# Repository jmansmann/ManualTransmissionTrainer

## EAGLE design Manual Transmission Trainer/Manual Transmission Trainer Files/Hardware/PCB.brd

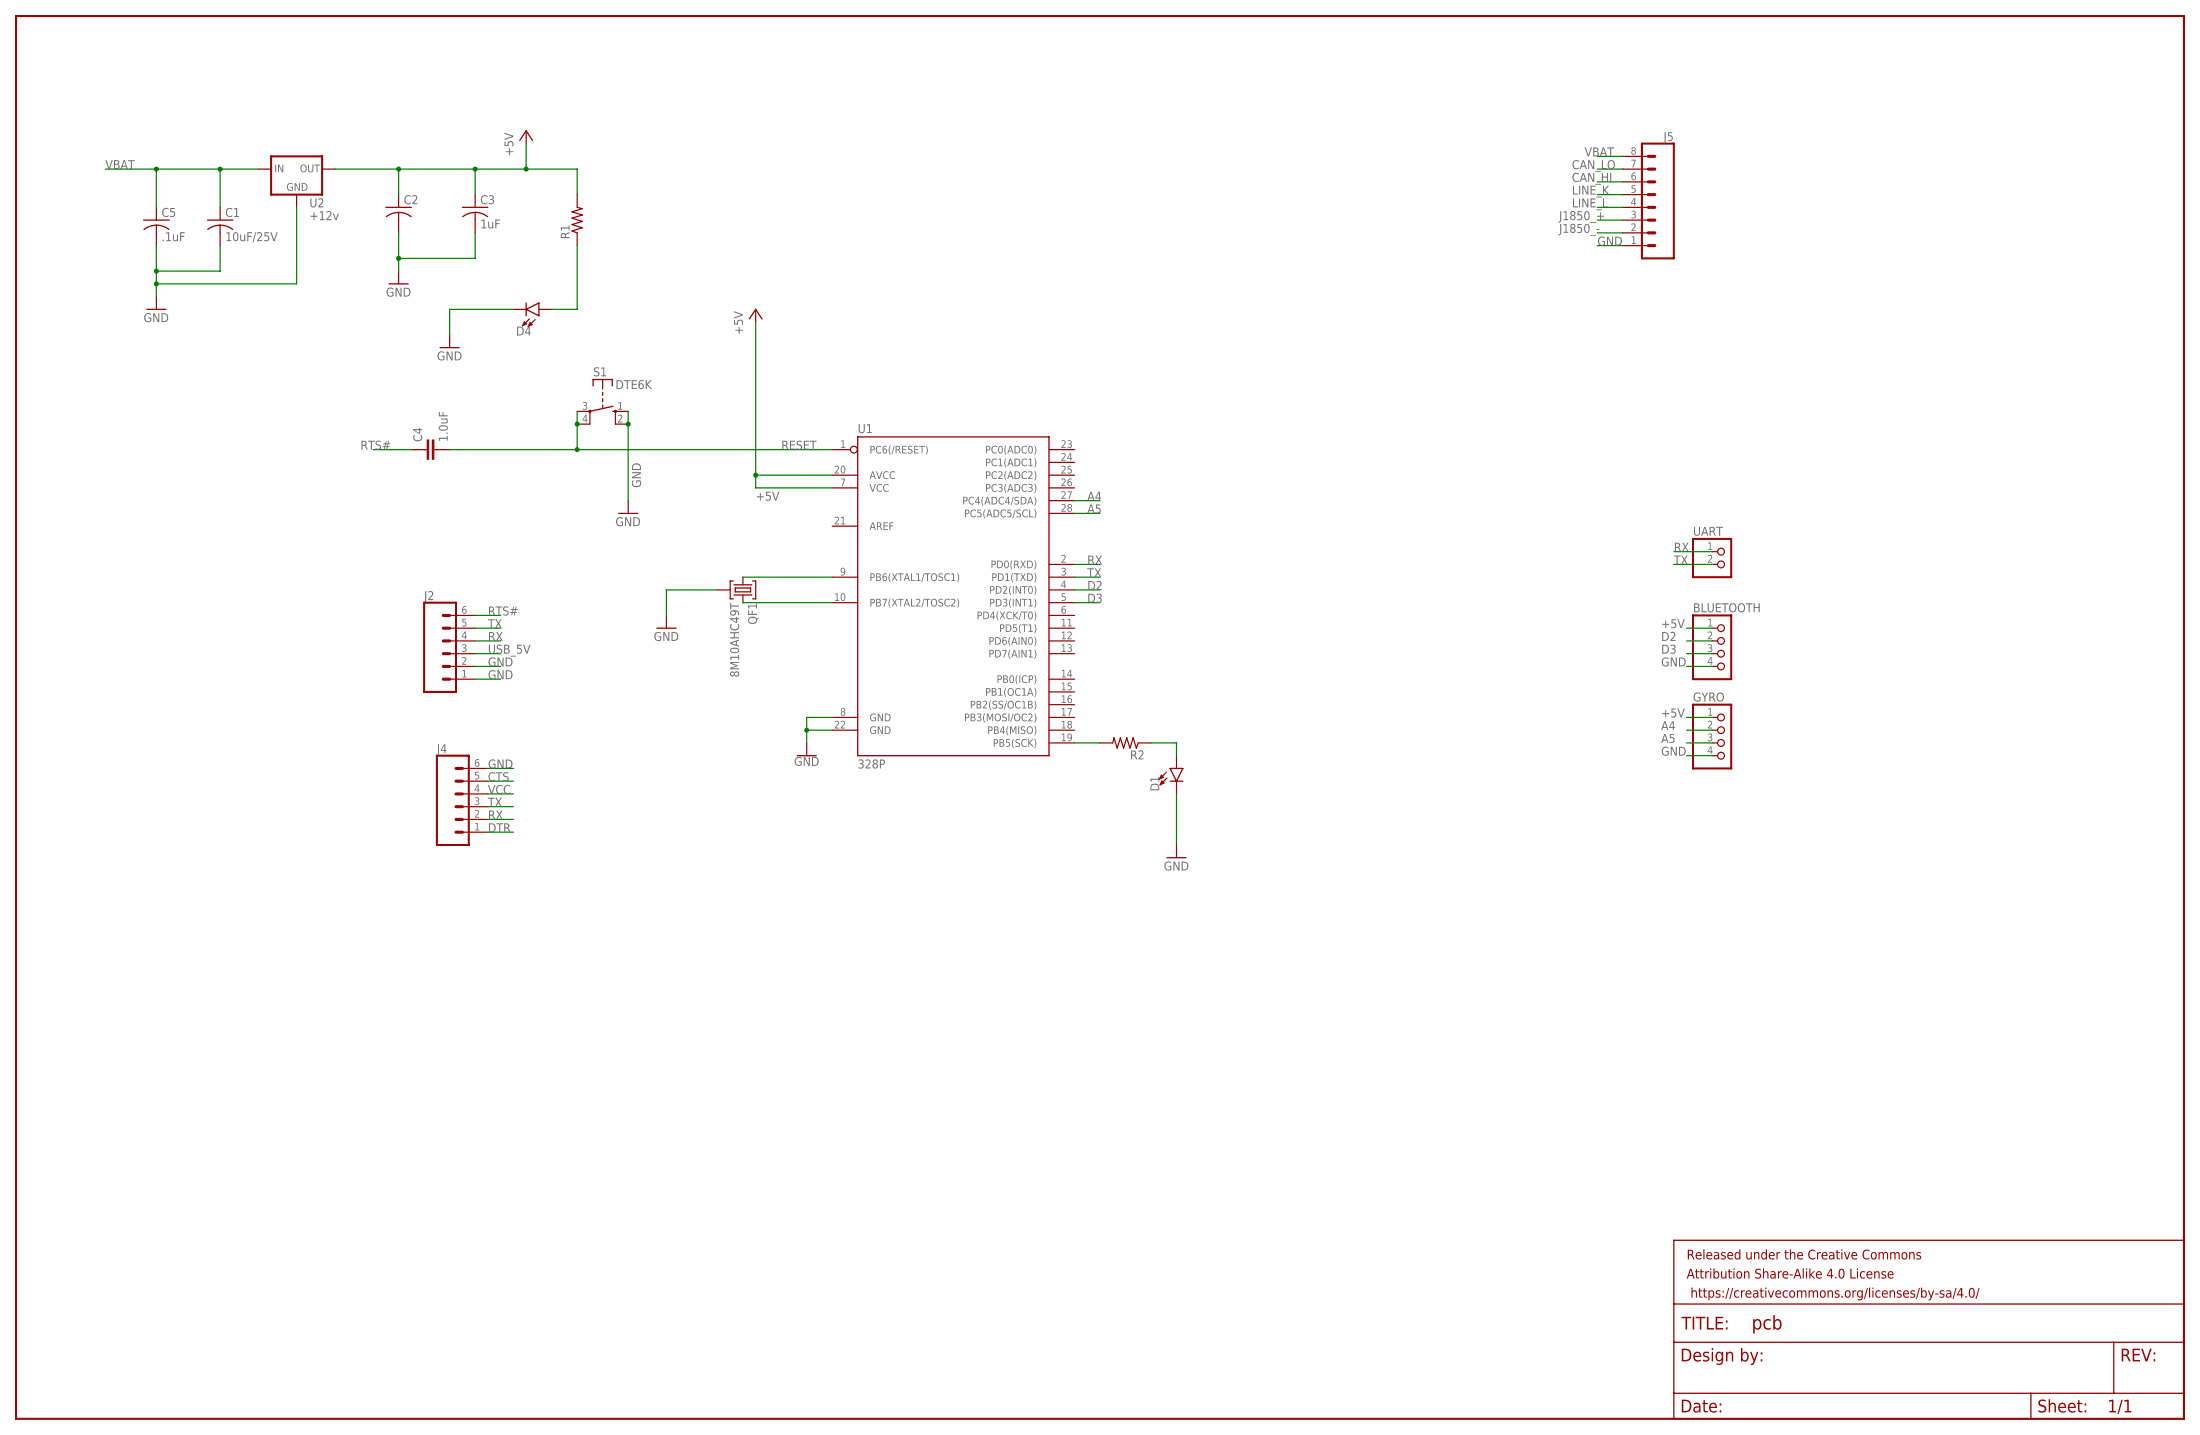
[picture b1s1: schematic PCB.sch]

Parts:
BLUETOOTH: PINHD-1X4; 1X04
C1: 10uF/25V; C050-025X075
C2: C-US050-025X075; C050-025X075
C3: 1uF; C050-025X075
C4: 1.0uF; 1206
C5: .1uF; C050-025X075
D1, D4: LED3MM; LED_3MM
FRAME1: FRAME-LEDGER; CREATIVE_COMMONS
GYRO: PINHD-1X4; 1X04
J2, J4: CONN_06LONGPADS; 1X06_LONGPADS
J5: CONN_08LONGPADS; 1X08_LONGPADS
QF1: 8M10AHC49T; HC49U
R1, R2: R-US_0204/5; 0204/5
S1: DTE6K
U1: 328P; DIP28
U2: +12v; TO-252
UART: PINHD-1X2; 1X02

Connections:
+5V: BLUETOOTH.1, C2.1, C3.1, GYRO.1, R1.2, U1.7 (VCC), U1.20 (AVCC), U2.2 (OUT)
A4: GYRO.2, U1.27 (PC4(ADC4/SDA))
A5: GYRO.3, U1.28 (PC5(ADC5/SCL))
CAN_HI: J5.6
CAN_LO: J5.7
CTS: J4.5
D2: BLUETOOTH.2, U1.4 (PD2(INT0))
D3: BLUETOOTH.3, U1.5 (PD3(INT1))
DTR: J4.1
GND: BLUETOOTH.4, C1.2, C2.2, C3.2, C5.2, D1.K (C), D4.K (C), GYRO.4, J2.1, J2.2, J4.6, J5.1, QF1.2, S1.1 (S), S1.2 (S), U1.8 (GND), U1.22 (GND), U2.3 (GND)
J1850_+: J5.3
J1850_-: J5.2
LINE_K: J5.5
LINE_L: J5.4
unnamed: QF1.1, U1.9 (PB6(XTAL1/TOSC1))
unnamed: QF1.3, U1.10 (PB7(XTAL2/TOSC2))
unnamed: R2.2, U1.19 (PB5(SCK))
unnamed: D1.A, R2.1
unnamed: D4.A, R1.1
RESET: C4.2, S1.3, S1.4, U1.1 (PC6(/RESET))
RTS#: C4.1, J2.6
RX: J2.4, J4.2, U1.2 (PD0(RXD)), UART.1
TX: J2.5, J4.3, U1.3 (PD1(TXD)), UART.2
USB_5V: J2.3
VBAT: C1.1, C5.1, J5.8, U2.1 (IN)
VCC: J4.4

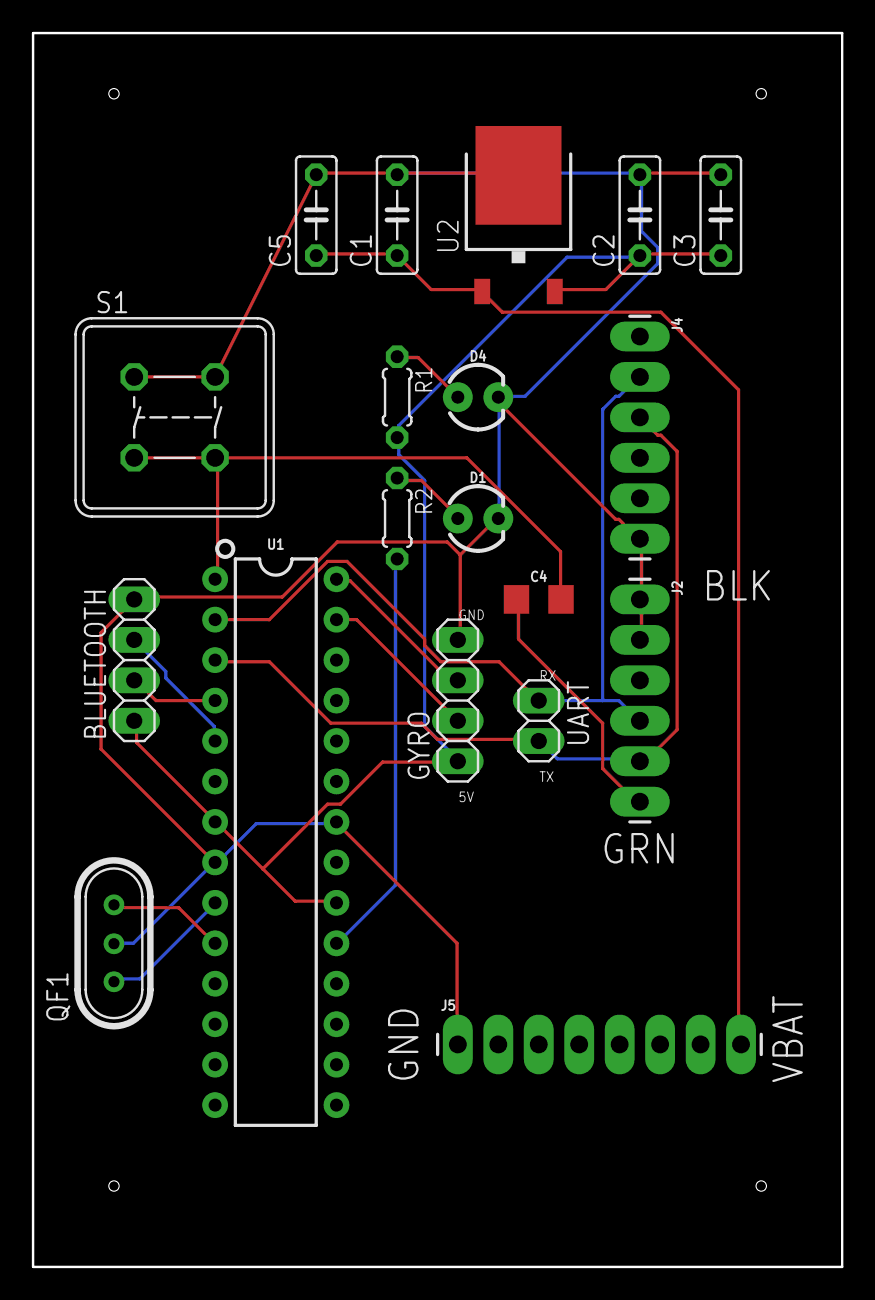
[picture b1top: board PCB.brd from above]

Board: 2 copper layers, 50.8 x 77.5 mm, 20 parts (0 on the bottom side), 16 nets.

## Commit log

2019-01-07 manual transmission trainer project

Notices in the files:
parts and their libraries:
SparkFun-Capacitors: Licensing: Creative Commons ShareAlike 4.0 International - https://creativecommons.org/licenses/by-sa/4.0
SparkFun-Aesthetics: Released under the Creative Commons Attribution Share-Alike 4.0 License
SparkFun-Aesthetics: https://creativecommons.org/licenses/by-sa/4.0
